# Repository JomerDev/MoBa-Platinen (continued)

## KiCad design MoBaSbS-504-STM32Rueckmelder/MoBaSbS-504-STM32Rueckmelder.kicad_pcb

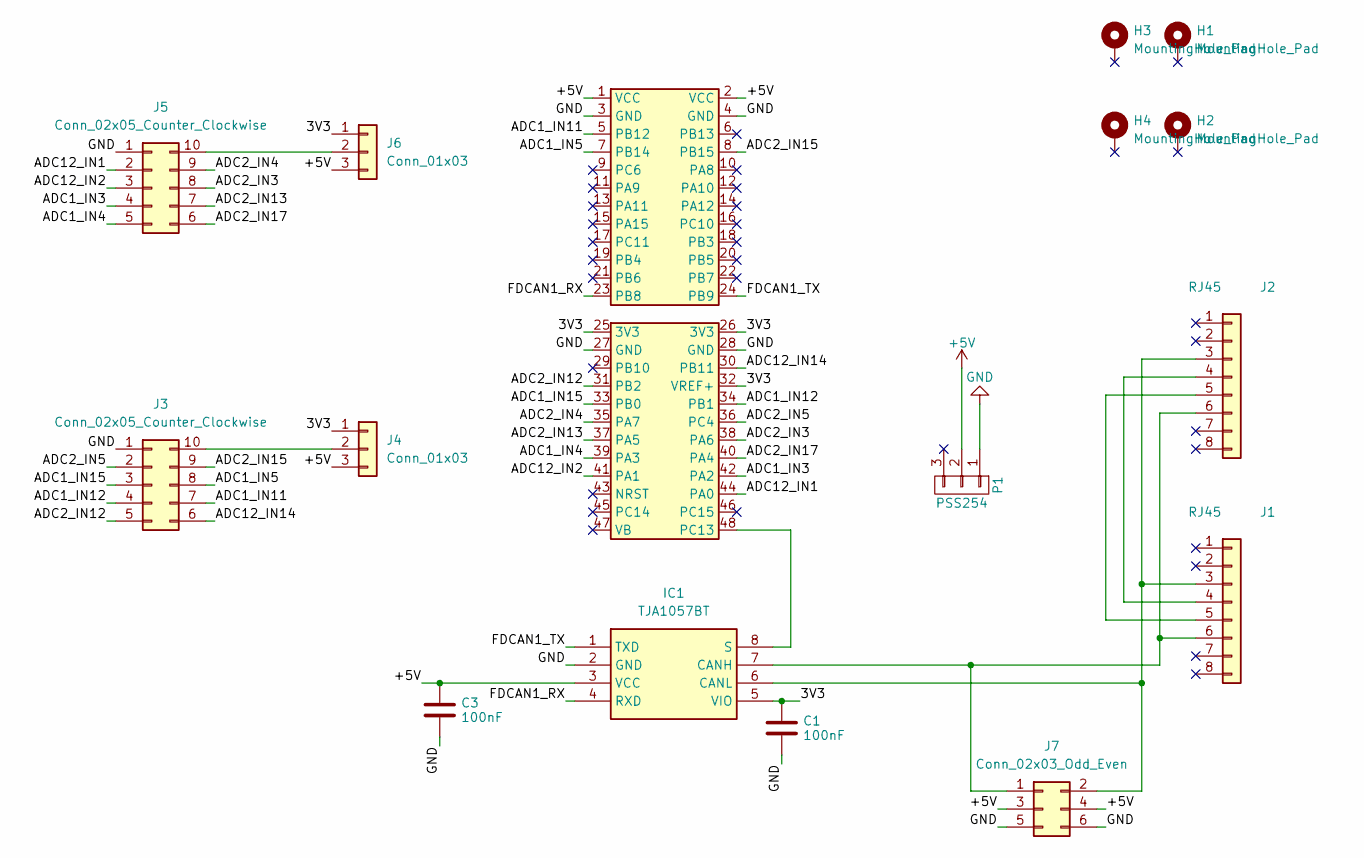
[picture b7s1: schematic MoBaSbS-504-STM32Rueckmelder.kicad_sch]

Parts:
C1, C3: 100nF; C_0603_1608Metric
H1, H2, H3, H4: MountingHole_Pad; MountingHole_2.7mm_M2.5_DIN965_Pad
IC1: TJA1057BT; SOIC127P600X175-8N; Manufacturer_Part_Number TJA1057BT
J1, J2: RJ45; RJ45_Amphenol_54602-x08_Horizontal
J3, J5: Conn_02x05_Counter_Clockwise; IDC-Header_2x05_P2.54mm_Vertical
J4, J6: Conn_01x03; PinHeader_1x03_P2.54mm_Vertical
J7: Conn_02x03_Odd_Even; PinHeader_2x03_P2.54mm_Horizontal
P1: PSS254; Molex_KK-254_AE-6410-03A_1x03_P2.54mm_Vertical
U1: WeAct-STM32G431

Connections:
+5V: C3.1, IC1.3 (VCC), J4.3, J6.3, J7.3, J7.4, P1.2, U1.1 (VCC), U1.2 (VCC)
/3V3: C1.1, IC1.5 (VIO), J4.1, J6.1, U1.25 (3V3), U1.26 (3V3), U1.32 (VREF+)
/ADC1_IN3: J5.4, U1.42 (PA2)
/ADC1_IN4: J5.5, U1.39 (PA3)
/ADC1_IN5: J3.8, U1.7 (PB14)
/ADC1_IN11: J3.7, U1.5 (PB12)
/ADC1_IN12: J3.4, U1.34 (PB1)
/ADC1_IN15: J3.3, U1.33 (PB0)
/ADC2_IN3: J5.8, U1.38 (PA6)
/ADC2_IN4: J5.9, U1.35 (PA7)
/ADC2_IN5: J3.2, U1.36 (PC4)
/ADC2_IN12: J3.5, U1.31 (PB2)
/ADC2_IN13: J5.7, U1.37 (PA5)
/ADC2_IN15: J3.9, U1.8 (PB15)
/ADC2_IN17: J5.6, U1.40 (PA4)
/ADC12_IN1: J5.2, U1.44 (PA0)
/ADC12_IN2: J5.3, U1.41 (PA1)
/ADC12_IN14: J3.6, U1.30 (PB11)
/FDCAN1_RX: IC1.4 (RXD), U1.23 (PB8)
/FDCAN1_TX: IC1.1 (TXD), U1.24 (PB9)
GND: C1.2, C3.2, IC1.2 (GND), J3.1, J5.1, J7.5, J7.6, P1.1, U1.3 (GND), U1.4 (GND), U1.27 (GND), U1.28 (GND)
unnamed: IC1.7 (CANH), J1.6, J2.6, J7.1
unnamed: IC1.6 (CANL), J1.3, J2.3, J7.2
unnamed: IC1.8 (S), U1.48 (PC13)
unnamed: J1.4, J2.4
unnamed: J1.5, J2.5
unnamed: J3.10, J4.2
unnamed: J5.10, J6.2

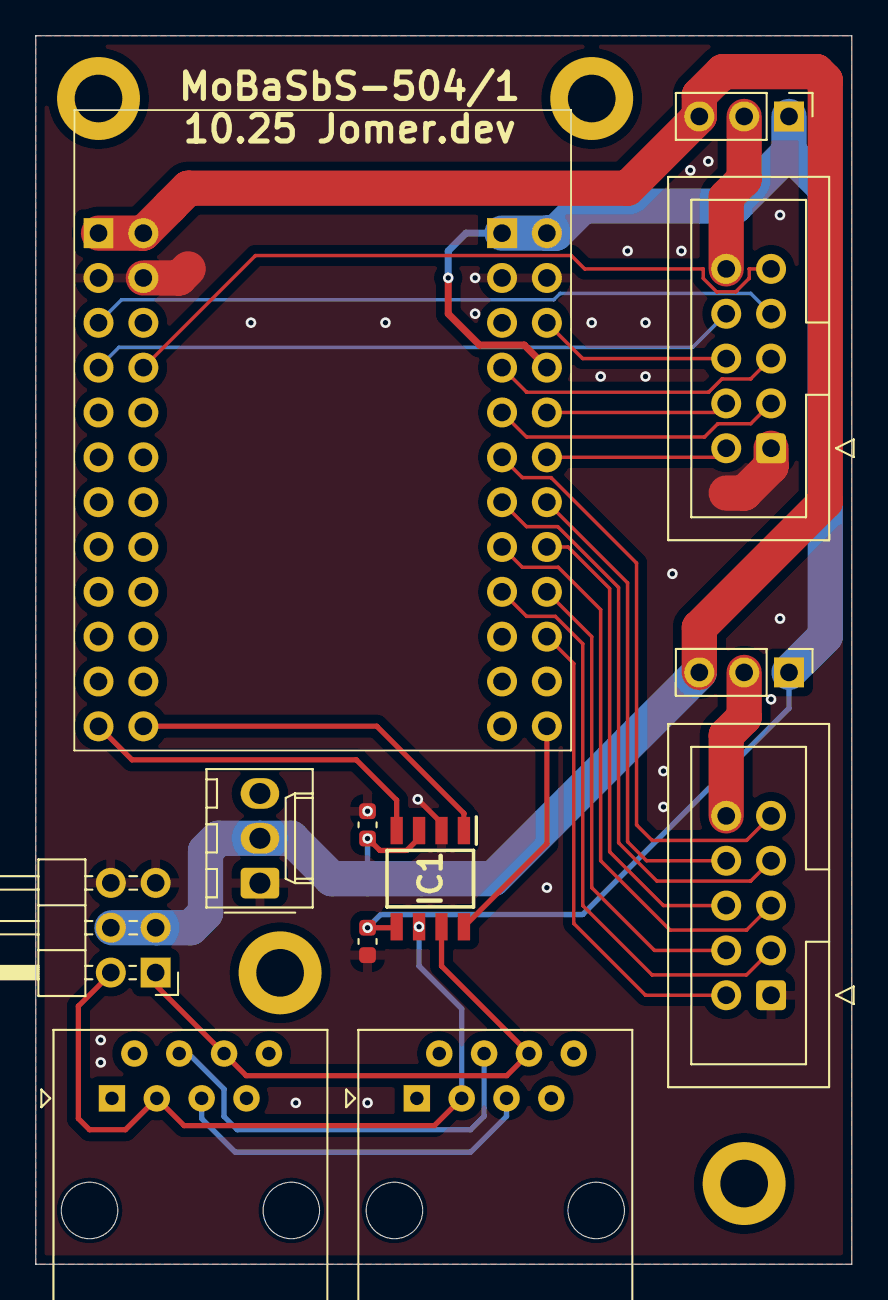
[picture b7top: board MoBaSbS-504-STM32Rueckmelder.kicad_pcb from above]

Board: 2 copper layers, 46.2 x 69.6 mm, 16 parts (0 on the bottom side), 28 nets.

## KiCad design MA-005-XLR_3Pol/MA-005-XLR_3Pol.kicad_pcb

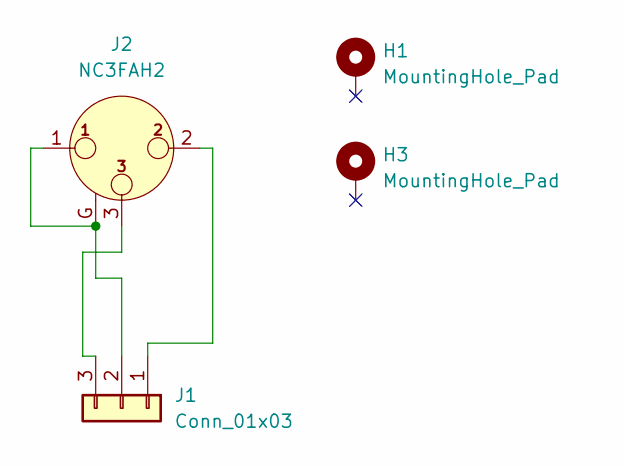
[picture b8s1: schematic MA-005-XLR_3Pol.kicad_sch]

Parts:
H1, H3: MountingHole_Pad; MountingHole_2.7mm_M2.5_DIN965_Pad
J1: Conn_01x03; Molex_KK-254_AE-6410-03A_1x03_P2.54mm_Vertical
J2: NC3FAH2; Jack_XLR_Neutrik_NC3FAH2_Horizontal

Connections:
unnamed: J1.1, J2.2
unnamed: J1.2, J2.1, J2.G
unnamed: J1.3, J2.3

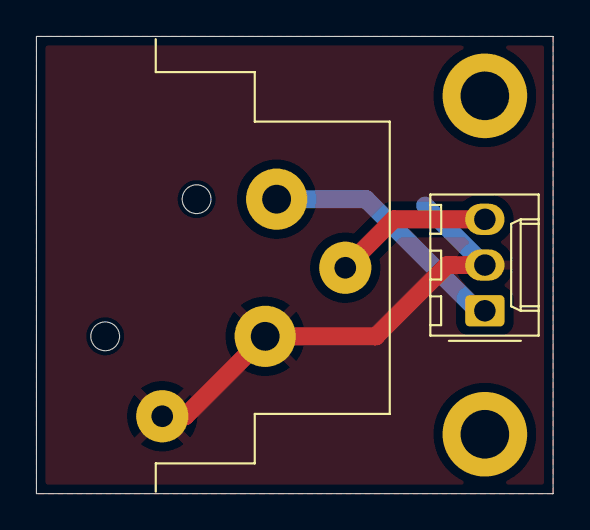
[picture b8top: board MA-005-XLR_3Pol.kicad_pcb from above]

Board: 2 copper layers, 28.7 x 25.4 mm, 4 parts (0 on the bottom side), 3 nets.

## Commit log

2025-03-20 Working on the MoBaSbS start PCB
2025-03-23 More work on that PCB, update to KiCad 9
2025-03-27 More work on the PCB
2025-07-31 Added a few PCBs
2025-10-06 Only some finishing touches left
2025-10-09 Some more work
2025-10-09 Finishing the dmx ethernet pico
2025-11-01 Generated panels, added some new PCBs
2025-11-06 Finished up PCBs, added stencil
2026-02-14 Latest changes
